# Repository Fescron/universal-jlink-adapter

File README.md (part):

# Universal J-Link Adapter

<br/>

<br/>

| Quick access links                                                                                                                                                                        |
| ----------------------------------------------------------------------------------------------------------------------------------------------------------------------------------------- |
| [Adapter v4.0 **schematic** (PDF)](hardware/jlink-tagConnect-adapter-v4/jlink-tagConnect-adapter-v4.pdf) // [Adapter v4.0 **gerber-files**](hardware/jlink-tagConnect-adapter-v4/Gerber/) |
| [Basic **J-Link Commander** usage and using **Segger Real-Time Transfer (RTT)** (instead of UART) for real-time debugging](JLinkExe-SeggerRTT-debugging-TipsTricks.md)                    |

<br/>

This multifunctional adapter board, primarily designed for use with a [J-Link debugger](https://www.segger.com/products/debug-probes/j-link/) (but others which follow the standard 20-pin JTAG/SWD pinout also work), allows the user to have the standard [9 pin Cortex-M SWD/JTAG pinout](https://www.segger.com/products/debug-probes/j-link/accessories/adapters/9-pin-cortex-m-adapter/) on both a 0.1" (2.54mm) and 0.05" (1.27mm) male pinheader. With additional jumpers it is possible to have **extra functionality** like **UART debugging though the J-Link's VCOM** on pins which normally aren't used in some modes, if the probe's hardware supports this. Good **labeling of all pin numbers and their corresponding functionality** also help to speed-up the embedded-development process. Additional information regarding the pinout of *default* SWD-headers as well as the voltage output of the J-Link debugger are also printed on the board, along with the pin-numbers of the [10 pin Tag-Connect header](http://www.tag-connect.com/TC2050-IDC).

Furthermore, the adapter PCB can **power the target board** through the `VTREF` connection. For this to work a **DC-DC converter or LDO regulator** can be plugged into the female 3-pin socket on the adapter board to allow the J-Link's 5V-Supply to be converted to, for example 3.3V. Various 3-pin voltage conversion boards are supported due to solder-jumpers available on the back of the adapter, allowing for the `VOUT`and `GND`pins to be swapped around. The 5V voltage can also be supplied *as-is* on a header pin by changing a jumper position.

Finally a physical reset button (with optional 100 Ω series-resistor and 100 nF filter capacitor) can be used to manually pull the reset line low, even if no debugger is connected. This eliminates the need to add a reset button to the target board and thus saves valuable board space.

The **0.05" (1.27mm) header** is recommended for when the target board is mostly connected to the debugger and the board in question also has a header of this size. The **0.1" (2.54mm) IDC header** is recommended for use with either regular jumper-wires or a [10 pin Tag-Connect adapter cable](http://www.tag-connect.com/TC2050-IDC). The latter allows target boards to be programmed without having to need a dedicated programming connector mounted, and thus saves on cost.

The figure on the left depicts the `TagConnect 2050` (*no-legs*) cable on the top-right, next to its corresponding footprint. Below this is a 0.05" header with its corresponding cable.

<br/>
<br/>

## 0 - Table of Contents

- [Universal J-Link Adapter](#universal-j-link-adapter)
  - [0 - Table of Contents](#0---table-of-contents)
  - [1 - Adapter functionality](#1---adapter-functionality)
    - [1.1 - Supply power to the target board (5V and/or other voltages)](#11---supply-power-to-the-target-board-5v-andor-other-voltages)
    - [1.2 - Additional functionality on "unused" pins using jumpers (and corresponding tips and tricks)](#12---additional-functionality-on-unused-pins-using-jumpers-and-corresponding-tips-and-tricks)
  - [2 - Serial flashing](#2---serial-flashing)
  - [3 - Layout guidelines for target boards](#3---layout-guidelines-for-target-boards)
  - [4 - BOM](#4---bom)
  - [5 - KiCad debug header symbols](#5---kicad-debug-header-symbols)

<br/>

## 1 - Adapter functionality

Aside from the ability to easily make connections to target boards using the well-labeled pinout and corresponding functionality of both output-headers, the following paragraphs give more information regarding additional features this adapter can provide.

<br/>

:pencil: **Note:** The pinout silkscreen has the following syntax:

- `... | ...`: The same (J-Link debugger) pin has different SWD or JTAG functionality
- `... / ...`: A jumper can be used to route one or the other signal to this pin
- `(...)`: This pin-signal deviates from the default SWD or JTAG pinout

<br/>

### 1.1 - Supply power to the target board (5V and/or other voltages)

As previously stated, a **DC-DC converter or LDO regulator** can be plugged into the 3-pin female header on this adapter with the labels `JP1 JP2 5V`. This would allow the adapter board to supply power through the `VTREF`-line (`PIN 1`) to the target board with the correct voltage, derived from the **5V supply of the J-Link debugger**. The 5V voltage can **also be made available *as-is* on** `PIN 5` of the output headers, by placing a jumper in the correct position of the header labeled `GND 5 5V`. With the same jumper `GND` can also be made available on `PIN 5`. Both the voltage-converter socket and `PIN 5`-jumper are depicted on the figure on the left.

If the user wishes to **not power the target board using** `VTREF`, for example in case of it already receiving power from a battery or external supply, the **voltage converter should simply not be plugged in**. The J-Link debugger will still receive the correct I/O voltage as a logic-level reference if the MCU's supply voltage is present on `VTREF` (`PIN 1`).

If the **pinout of the 3-pin voltage converter doesn't match** `VIN - VOUT - GND`, the last two pins can be changed around by swapping the solder joints on `JP1` and `JP2` on the bottom of the PCB. This is also also depicted on the figure on the left. If the present copper traces are cut on both jumpers and new solder connections are made on the opposite side, the pinout `VIN - GND - VOUT` will be selected.

<br/>

The **5V output needs to be enabled on the J-Link** using the [J-Link Commander](https://kb.segger.com/J-Link_Commander) software (`JLink.exe/JLinkExe`). The following command needs to be executed for the 5V supply to be always enabled:

```shell
Power On perm
```

<br/>

If the target board is powered via a voltage-converter on the adapter PCB, a jumper labeled `VTREF 1` below the 0.1" header allows for a **current meter** to be inserted between the converter and target board. This way its power usage can be monitored, for example in case the J-Link probe doesn't have this functionality build-in. If 5V is supplied to the target board through `PIN 5`, a jumper in this location can also be substituted for a current meter. Both headers are depicted on the figure on the right.

<br/>

### 1.2 - Additional functionality on "unused" pins using jumpers (and corresponding tips and tricks)

In addition to the *default* SWD or JTAG pinouts it is also possible to add extra functionality to normally *unused* pins of the 02x05 headers:

- :pushpin: **PIN 5** is normally connected to `GND`.
  - On the [Segger 10 pin Needle Adapter](https://www.segger.com/products/debug-probes/j-link/accessories/adapters/10-pin-needle-adapter/) this pin outputs the J-Link's `5V-Supply`. A jumper on the adapter board can be used to select this, which was already mentioned in the previous section.
  - :bulb: **TIP:** See the [following section](#2---serial-flashing) to use this pin for **serial programming**.
- :pushpin: **PIN 6** is normally used for the `SWO` or `TDO` connection. A jumper labeled `SWO TDO 6`, which can be seen on the figure on the right, can however be used to disconnect the debugger from the target board.
  - :bulb: **TIP:** Disconnecting the pin from the debugger can enable the MCU's output pin to be used as a GPIO debug signal. It can for example be set high if some code is running, and low when this is not the case. Simply remove the jumper and add a jumper-wire on the pin labeled `6`.
- :pushpin: **PIN 7** is on the [standard 9-pin Cortex-M SWD/JTAG pinout](https://www.segger.com/products/debug-probes/j-link/accessories/adapters/9-pin-cortex-m-adapter/) *not populated* since this is the **key**.
  - **SWD mode:** A jumper labeled `RTCK 7 JL.RX` can be used to connect this pin to the J-Link's **VCOM** `RX` pin. This way UART debugging can be used in conjunction with SWD.
    - :bulb: **TIP:** The jumper can also be removed, and a separate UART `TXD` signal from a target board can be connected to the J-Link's `RX` input by connecting a jumper-wire to the `JL.RX` pin.
    - :pencil: **NOTE:** It is possible VCOM needs to be enabled on the probe. This can be done using [J-Link Commander](https://kb.segger.com/J-Link_Commander) (`JLinkExe/JLink.exe`) by executing the following command (VCOM will start working after the next power-cycle):
      ```shell
      VCOM enable
      ```
  - **JTAG mode:** The same jumper can also be used to connect this pin to `RTCK` if necessary.
- :pushpin: **PIN 8**
  - **SWD mode:** Normally this pin is *not connected*, but a jumper labeled `JL.TX TDI 8` allows it to be connected to the J-Link's **VCOM** `TX` pin.
    - :bulb: **TIP:** The jumper can also be removed, and a separate UART `RXD` signal from a target board can be connected to the J-Link's `TX` output by connecting a jumper-wire to the `JL.TX` pin.
  - **JTAG mode:** On Segger's [9 pin](https://www.segger.com/products/debug-probes/j-link/accessories/adapters/9-pin-cortex-m-adapter/) and [19 pin](https://www.segger.com/products/debug-probes/j-link/accessories/adapters/19-pin-cortex-m-adapter/) Cortex-M adapters `PIN 9` is connected to `TDI`.
    - :bulb: **TIP:** The `TDI` signal of a J-Link debugger can be set *low* or *high* using **J-Link Commander** by executing `TDI0` and `TDI1` respectively, even if there is no target connection active. This signal can thus be used as a GP(I)O line to, for example, an MCU input pin.
  - :pencil: **NOTE:** `JL.TX` and `TDI` are for both modes located on the same physical J-Link pin. This means the jumper should normally not need to be disconnected when using the adapter in one or the other mode.
- :pushpin: **PIN 9**
  - **SWD mode:** Normally this pin is *not connected*. Sometimes a target board however uses this pin as `GNDdetect`, so it can (as the name implies) detect the presence of a debugger. With a jumper labeled `nTRST 9 GND` this pin can be connected to `GND` to enable this functionality.
    - :bulb: **TIP:** When `PIN 9` is connected to a microcontroller pin which can act as an output, the adapter can be used to *break-out* this pin to another instrument for, for example, code-timing analysis. Simply remove the jumper and add a jumper-wire on the pin labeled `9`.
  - **JTAG mode:** On Segger's [9 pin](https://www.segger.com/products/debug-probes/j-link/accessories/adapters/9-pin-cortex-m-adapter/) and [19 pin](https://www.segger.com/products/debug-probes/j-link/accessories/adapters/19-pin-cortex-m-adapter/) Cortex-M adapters this pin can be connected to `nTRST` using a solder jumper. On this adapter board this can be done using a regular jumper.
    - :bulb: **TIP:** The `nTRST` signal of a J-Link debugger can be set *low* or *high* using **J-Link Commander** by executing `TRST0` and `TRST1` respectively, even if there is no target connection active. This signal can thus be used as a GP(I)O line to, for example, an MCU input pin.
- :pushpin: **PIN 10** is used to reset the target board. A jumper is present to disconnect this line if necessary.
  - :bulb: **TIP:** The `nRESET` signal of a J-Link debugger can be set *low* or *high* using **J-Link Commander** by executing `R0` and `R1` respectively, even if there is no target connection active.<br/>
  - An `nRESET` button is also present on the adapter board to manually pull the reset line low. An optional (100 Ω) series-resistor `R1` and (100 nF) filter capacitor C1 can be mounted on the bottom of the board, both in the 0603 package. They are depicted on the figure on the right. To *activate* the functionality of `R1` jumper `JP10` has to be cut.

<br/>

:bulb: **TIP:** `ShowHWStatus` or `ST` can be executed in **J-Link Commander** to show the current `VTREF` voltage as well as the signal-level of the `SWCLK|TCK`, `TDI`, `SWO|TDO`, `SWDIO|TMS`, `nRESET` (`TRES`) and `nTRST` pins, even if there is no target connection active.

Additionally a two-pin `GND` header, next to the `JL.TX TDI 8` jumper, also facilitates some additional ground-wire connections for general debug connections.

<br/>

<br/>

## 2 - Serial flashing

Due to the availability of the jumpers on the adapter PCB certain pins can also be used to detect if a target board is plugged in. A board such as the [Macropedal](https://github.com/Fescron/macropedal) can for example be used to check if `pin 5` is, via a target board, connected to ground. If this is the case, the *Macropedal* can enter a command in a terminal to flash firmware to a board. This way one after the other board can be programmed in a **series production** scenario. The target board can even be powered by the adapter itself for a complete *stand-alone* setup. The figure on the right depicts such an arrangement. Refer to [Segger J-Link debugging tips & tricks - 2 - Scripting](JLinkExe-SeggerRTT-debugging-TipsTricks.md#2---scripting) for more information.

<br/>

## 3 - Layout guidelines for target boards

It is advised to add the following passives to the *target board* for protection and stability. This is also mentioned on the [adapter schematic](hardware/jlink-tagConnect-adapter-v4/jlink-tagConnect-adapter-v4.pdf).

- 10 kΩ pullup on `SWDIO|TMS`, `TDO` and `TDI` (and the target board's `RXD` line)
- 10 kΩ pulldown on `SWCLK|TCK`
- 33 to 100 Ω in-line current-limiting resistors on `TXD` and `RXD` lines
  - This can be important for when UART is available on a (0.1") external header, and is less important if this is made available on the SWD-header. 100 pF capacitors (*after* the series resistors) can also help with some filtering and ESD mitigation.

<br/>

## 4 - BOM

| Component              | Footprint                                                | Manufacturer `Partnumber`      | Ordering                                                                                                                 |
| ---------------------- | -------------------------------------------------------- | ------------------------------ | ------------------------------------------------------------------------------------------------------------------------ |
| J1                     | 02x10 0.1" (2.54mm) Right Angle Keyed Female IDC Socket  | Sullins `SFH11-PBPC-D10-RA-BK` | [digikey.be](https://www.digikey.be/product-detail/en/sullins-connector-solutions/SFH11-PBPC-D10-RA-BK/S9205-ND/1990098) |
| J2                     | 02x05 0.1" Male Key-Shrouded IDC Header                  | Samtec `TST-105-01-L-D`        | [digikey.be](https://www.digikey.be/en/products/detail/samtec-inc/TST-105-01-L-D/2685818)                                |
| J3                     | 02x05 0.05" (1.27mm) Male Key-Shrouded Header            | Samtec `FTSH-105-01-L-D-K`     | [digikey.be](https://www.digikey.be/en/products/detail/samtec-inc/FTSH-105-01-L-D-K/2649979)                             |
| J4                     | 01x03 0.1" Female IDC Socket                             | Samtec `SSW-103-01-G-S`        | [digikey.be](https://www.digikey.be/en/products/detail/samtec-inc/SSW-103-01-G-S/1112104)                                |
| J5, JP4, JP5, JP8, JP9 | 01x02 0.1" Male IDC Header                               | Samtec `TSW-102-07-L-S`        | [digikey.be](https://www.digikey.be/en/products/detail/samtec-inc/TSW-102-07-L-S/1101425)                                |
| JP3, JP6, JP7          | 01x03 0.1" Male IDC Header                               | Samtec `TSW-103-07-L-S`        | [digikey.be](https://www.digikey.be/en/products/detail/samtec-inc/TSW-103-07-L-S/1101424)                                |
| SW1                    | 6.5mm Pitch Through-hole Switch                          | C&K `PTS636SL43 LFS`           | [digikey.be](https://www.digikey.be/en/products/detail/c-k/PTS636SL43-LFS/10071714)                                      |
| R1                     | 100 Ω 0603 1% (1 kΩ should also work)                    | Yageo `RC0603FR-07100RL`       | [digikey.be](https://www.digikey.be/en/products/detail/yageo/RC0603FR-07100RL/726888)                                    |
| C1                     | 100 nF 0603 10% 50V X7R                                  | Yageo `CC0603KRX7R9BB104`      | [digikey.be](https://www.digikey.be/en/products/detail/yageo/CC0603KRX7R9BB104/2103082)                                  |
|                        | 2.54mm Pitch Jumpers                                     | Samtec `SNT-100-BK-G`          | [digikey.be](https://www.digikey.be/en/products/detail/samtec-inc/SNT-100-BK-G/1756763)                                  |
|                        | 02x05 0.05" IDC Cable, 6 inch (15 cm) Long               | Samtec `FFSD-05-D-06.00-01-N`  | [digikey.be](https://www.digikey.be/en/products/detail/samtec-inc/FFSD-05-D-06-00-01-N/1106577)                          |
|                        | TagConnect 10 pin IDC to Needles Without Legs (`...-NL`) | TagConnect `TC-2050-IDC-NL`    | [digikey.be](https://www.digikey.be/product-detail/nl/tag-connect-llc/TC2050-IDC-NL/TC2050-IDC-NL-ND/2605367)            |
|                        | TagConnect 10 pin IDC to Needles                         | TagConnect `TC-2050-IDC`       | [digikey.be](https://www.digikey.be/en/products/detail/tag-connect-llc/TC2050-IDC/2605366)                               |

<br/>

## 5 - KiCad debug header symbols

On the repository [brechtve-kicad-things](https://github.com/Fescron/brechtve-kicad-things) symbols are available where the additional functionality, selectable using the jumpers, is depicted for both SWD and JTAG modes. The *regular* pinouts are put into brackets. The symbols can be found in the library [`BrechtVE_DebugHeader.lib`](https://github.com/Fescron/brechtve-kicad-things/blob/master/Libraries/BrechtVE_DebugHeader.lib).

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
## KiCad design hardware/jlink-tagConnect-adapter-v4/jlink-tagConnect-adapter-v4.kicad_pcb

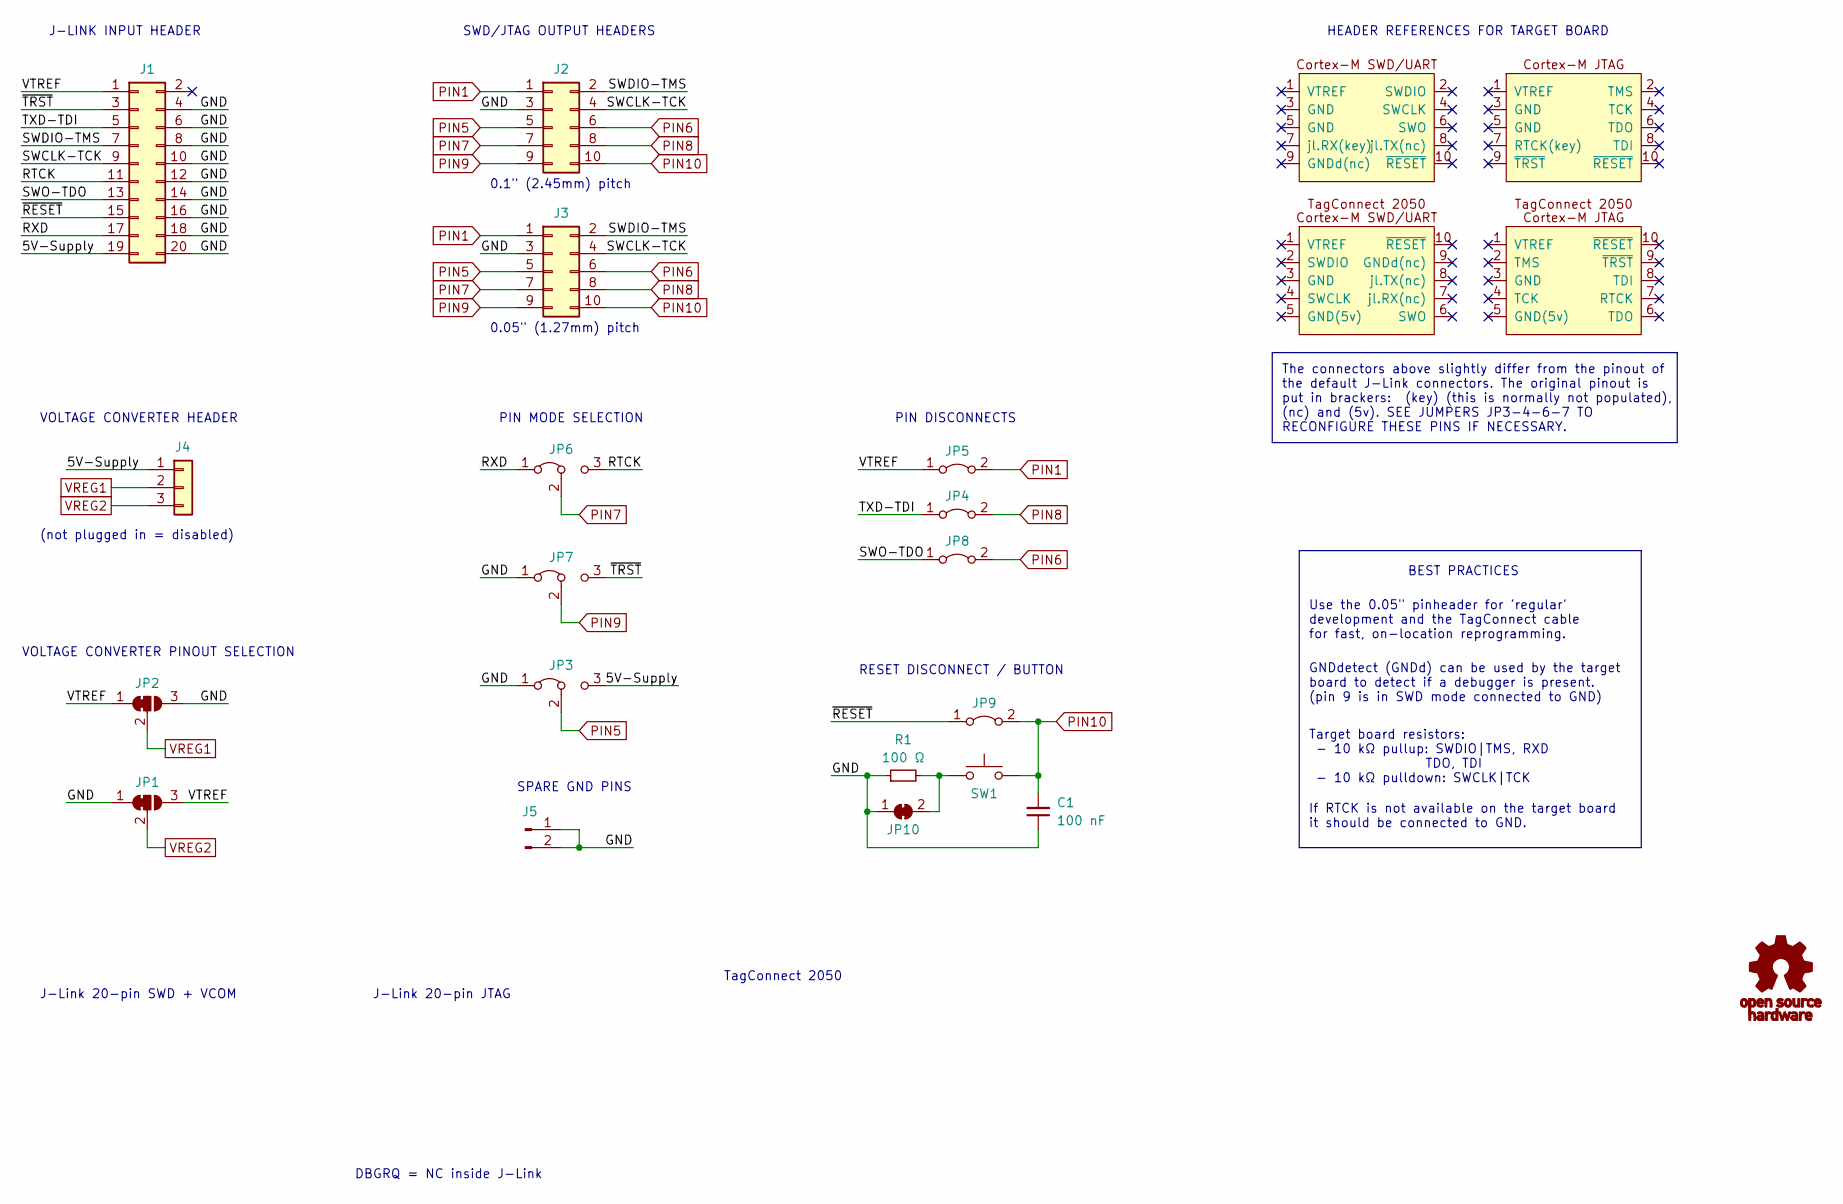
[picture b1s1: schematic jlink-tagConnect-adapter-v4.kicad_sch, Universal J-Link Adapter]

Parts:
C1: 100 nF; C_0603_1608Metric_Pad1.08x0.95mm_HandSolder
G1: Symbol_OSHW-Logo_11.4x12mm; OSHW-Logo_5.7x6mm_SolderMask
J1: Conn_02x10_Odd_Even; PinSocket_2x10_P2.54mm_Horizontal
J2: Conn_02x05_Odd_Even; IDC-Header_2x05_P2.54mm_Vertical
J3: Conn_02x05_Odd_Even; PinHeader_2x05_P1.27mm_Vertical
J4: Conn_01x03; PinSocket_1x03_P2.54mm_Vertical
J5: Conn_01x02_Pin; PinHeader_1x02_P2.54mm_Vertical
JP1, JP2: SolderJumper_3_Bridged12; SolderJumper-3_P1.3mm_Bridged12_Pad1.0x1.5mm_NumberLabels
JP3, JP6, JP7: Jumper_3_Bridged12; PinHeader_1x03_P2.54mm_Vertical
JP4, JP5, JP8, JP9: Jumper_2_Bridged; PinHeader_1x02_P2.54mm_Vertical
JP10: SolderJumper_2_Bridged; SolderJumper-2_P1.3mm_Bridged_Pad1.0x1.5mm
R1: 100 Ω; R_0603_1608Metric_Pad0.98x0.95mm_HandSolder
SW1: SW_Push; SW_PUSH_1P1T_6x3.5mm_H4.3_APEM_MJTP1243

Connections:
/5V-Supply: J1.19, J4.1, JP3.3 (B)
/GND: C1.1, J1.4, J1.6, J1.8, J1.10, J1.12, J1.14, J1.16, J1.18, J1.20, J2.3, J3.3, J5.1, J5.2, JP1.1 (A), JP2.3 (B), JP3.1 (A), JP7.1 (A), JP10.1 (A), R1.1
/RTCK: J1.11, JP6.3 (B)
/RXD: J1.17, JP6.1 (A)
/SWCLK-TCK: J1.9, J2.4, J3.4
/SWDIO-TMS: J1.7, J2.2, J3.2
/SWO-TDO: J1.13, JP8.1 (A)
/TXD-TDI: J1.5, JP4.1 (A)
/VTREF: J1.1, JP1.3 (B), JP2.1 (A), JP5.1 (A)
/~RESET: J1.15, JP9.1 (A)
/~TRST: J1.3, JP7.3 (B)
unnamed: JP10.2 (B), R1.2, SW1.1
PIN1: J2.1, J3.1, JP5.2 (B)
PIN5: J2.5, J3.5, JP3.2 (C)
PIN6: J2.6, J3.6, JP8.2 (B)
PIN7: J2.7, J3.7, JP6.2 (C)
PIN8: J2.8, J3.8, JP4.2 (B)
PIN9: J2.9, J3.9, JP7.2 (C)
PIN10: C1.2, J2.10, J3.10, JP9.2 (B), SW1.2
VREG1: J4.2, JP2.2 (C)
VREG2: J4.3, JP1.2 (C)

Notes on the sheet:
(not plugged in = disabled)
VOLTAGE CONVERTER PINOUT SELECTION
TagConnect 2050
GNDdetect (GNDd) can be used by the target board to detect if a debugger is present. (pin 9 is in SWD mode connected to GND)
0.1" (2.45mm) pitch
PIN DISCONNECTS
0.05" (1.27mm) pitch
SPARE GND PINS
BEST PRACTICES
RESET DISCONNECT / BUTTON
PIN MODE SELECTION
DBGRQ = NC inside J-Link
The connectors above slightly differ from the pinout of the default J-Link connectors. The original pinout is put in brackers: (key) (this is normally not populated), (nc) and (5v). SEE JUMPERS JP3-4-6-7 TO RECONFIGURE THESE PINS IF NECESSARY.
SWD/JTAG OUTPUT HEADERS
J-Link 20-pin JTAG
J-LINK INPUT HEADER
HEADER REFERENCES FOR TARGET BOARD
VOLTAGE CONVERTER HEADER
If RTCK is not available on the target board it should be connected to GND.
Use the 0.05" pinheader for 'regular' development and the TagConnect cable for fast, on-location reprogramming.
J-Link 20-pin SWD + VCOM
Target board resistors: - 10 kΩ pullup: SWDIO|TMS, RXD TDO, TDI - 10 kΩ pulldown: SWCLK|TCK

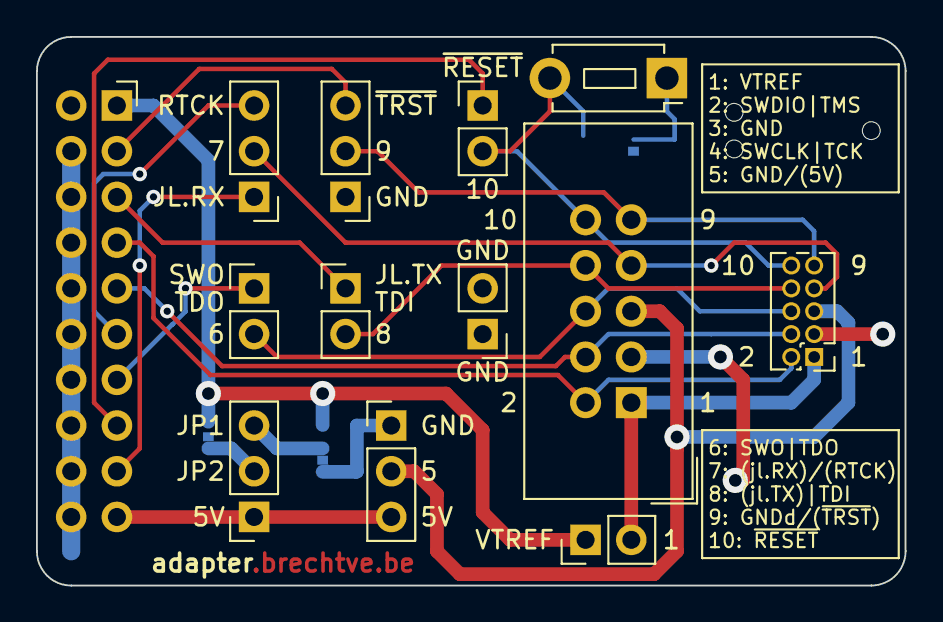
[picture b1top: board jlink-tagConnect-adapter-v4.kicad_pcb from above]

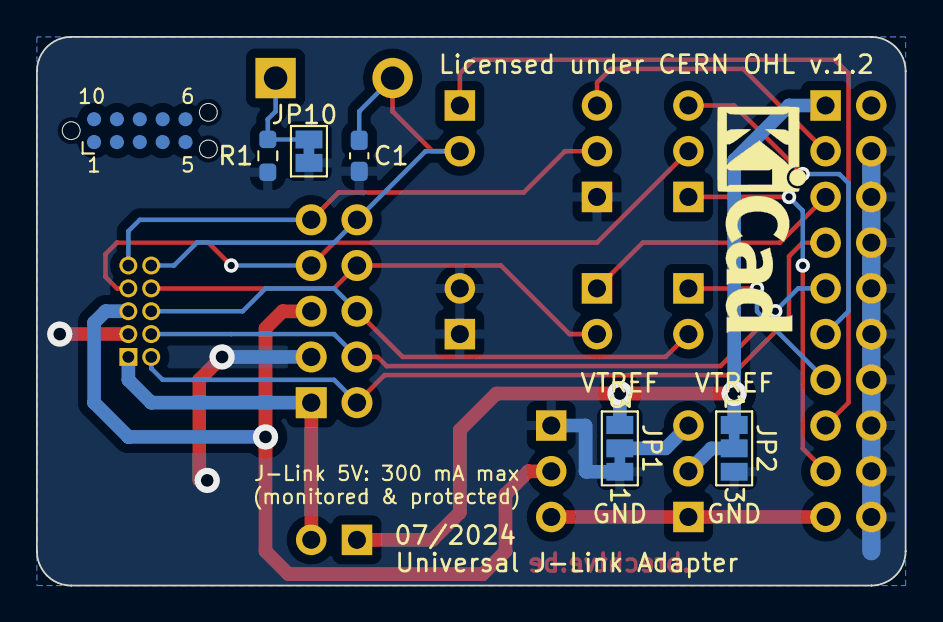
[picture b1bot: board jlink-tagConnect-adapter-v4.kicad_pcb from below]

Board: 2 copper layers, 48.3 x 30.5 mm, 19 parts (6 on the bottom side), 21 nets.

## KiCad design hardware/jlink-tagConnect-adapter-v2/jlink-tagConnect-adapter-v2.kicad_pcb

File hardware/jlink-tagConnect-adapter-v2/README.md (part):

# Universal J-Link Adapter

<br/>

<br/>

- [Quick link to the schematic](hardware/jlink-tagConnect-adapter-v2/jlink-tagConnect-adapter-v2.pdf)

<br/>

This multifunctional adapter board, primarily designed for use with a [J-Link debugger](https://www.segger.com/products/debug-probes/j-link/models/j-link-base/) (or others which follow its standard 20-pin JTAG/SWD pinout), allows the user to have the standard [9 pin Cortex-M SWD/JTAG pinout](https://www.segger.com/products/debug-probes/j-link/accessories/adapters/9-pin-cortex-m-adapter/) on both a 0.1" (2.54mm) and 0.05" (1.27mm) header. With additional jumpers, it's possible to have **extra options (for example UART debugging though the J-Link's VCOM) on pins that normally aren't used in some modes**. The adapter can also **power the target board** through `VTREF`. A DC-DC converter can be plugged in on the adapter to allow the J-Link's `5V-Supply` to be converted to, for example 3.3V.

The **0.05" header** is recommended for development when the target board is mostly connected to the debugger. The **0.1" IDC header** is recommended for use with a [10 pin Tag-Connect adapter cable](http://www.tag-connect.com/TC2050-IDC), so target boards can quickly be reprogrammed *on-location*.

On the picture next to this text on top you can see this TagConnect 2050 cable next to its corresponding PCB footprint. Below you can see the 0.05" header with its corresponding cable.

<br/>

A lot of useful information is also printed on the *silkscreen* of the PCB. Noteworthy is the **pinout numbering** of the 0.1" and 0.05" headers (wich are connected to SWD/JTAG pins) and also the numbering of the 10-pin Tag-Connect header on the front. The **functions for every pin** are also printed on the back of the PCB.

<br/>

## 1 - Functions

### 1.1 - Supply power to a target board

A **DC-DC converter** can be plugged in on the header with the labels `5V JP6 JP7` to supply the target board with the correct voltage, derived from the 5V supply of the J-Link programmer. If the pinout of the converter doesn't match `VIN - VOUT - GND`, the last two pins can be changed around by swapping the solder joints on `JP6` and `JP7` on the bottom of the PCB. Then the pinout `VIN - GND - VOUT` will be selected.

This 5V output needs to be enabled on the J-Link using the `J-Link Commander` (`JLinkExe`) software. The following command needs to be called for the 5V supply to be always enabled:

```shell
power on perm
```

If the user wishes to **not power the target board using `VTREF`** (for example in the case that the target board is already getting its own power from a battery), the **DC-DC converter should simply not be plugged in**.

<br/>

**PIN 1** (`VTREF`) normally supplies the J-Link adapter with a voltage to allow it to generate the correct logic levels. With this adapter board the target board can be powered through `VTREF` using the previously mentioned DC-DC converter. A jumper is supplied below the 0.1" header to allow a **current meter** to be plugged in-line between the DC-DC converter and the target board so the power usage can be monitored.

<br/>

### 1.2 - Additional functionality on unused pins using jumpers

- **PIN 5** is normally connected to GND.
  - On the [J-Link 10 pin Needle Adapter](https://www.segger.com/products/debug-probes/j-link/accessories/adapters/10-pin-needle-adapter/) this pin outputs the J-Link's `5V-Supply`. A jumper can be used to select this.
- **PIN 7** is on the [standard 9-pin Cortex-M SWD/JTAG pinout](https://www.segger.com/products/debug-probes/j-link/accessories/adapters/9-pin-cortex-m-adapter/) *not populated* since this is the **key**.
  - **SWD mode:** A jumper can be used to connect this pin to the J-Link's VCOM `RX` pin, so UART debugging functionality can be used in conjunction with SWD.
  - **JTAG mode:** The same jumper can also be used to connect this pin to `RTCK` if necessary.
- **PIN 8**
  - **SWD mode:** Normally this pin is *not connected*, but a jumper allows it to be connected to the J-Link's VCOM `TX` pin.
  - **JTAG mode:** On J-Link's [9 pin](https://www.segger.com/products/debug-probes/j-link/accessories/adapters/9-pin-cortex-m-adapter/) and [19 pin](https://www.segger.com/products/debug-probes/j-link/accessories/adapters/19-pin-cortex-m-adapter/) Cortex-M adapters this pin is connected to `TDI`.
  - *NOTE:* `TX` and `TDI` are in both modes on the same pin. This means that normally this pin shouldn't be disconnected but a jumper allows this just in case.
- **PIN 9**
  - **SWD mode:** Normally this pin is *not connected*, but sometimes a target board uses this pin as `GNDdetect` so it can detect the presence of a debugger. With a jumper this pin can be connected to GND to enable this functionality.
  - **JTAG mode:** On J-Link's [9 pin](https://www.segger.com/products/debug-probes/j-link/accessories/adapters/9-pin-cortex-m-adapter/) and [19 pin](https://www.segger.com/products/debug-probes/j-link/accessories/adapters/19-pin-cortex-m-adapter/) Cortex-M adapters this pin can be connected to `nTRST` using a solder jumper. On this adapter board this can be done using a regular jumper.

<br/>

## 2 - KiCad debug header symbols

On the repository [brechtve-kicad-things](https://github.com/Fescron/brechtve-kicad-things) (kicad.brechtve.be) you can find some symbols (and a lot of additional information regarding KiCad) where these additional functions, selectable using the jumpers, are depicted for both SWD and JTAG modes. They can be found in the library `BrechtVE_DebugHeader.lib`. The symbols can be linked to a 0.05" header on the target board and are:

<br/>
<br/>

Symbols are also supplied that can be linked to a TagConnect 2050 footprint. The pin numbers and corresponding functions are mostly the same as the previously mentioned SWD/JTAG connectors, but the direction in wich the pins are layed out on the PCB are different. This is reflected in other symbols:

<br/>
<br/>

For reference, these symbols (and additional information regarding for example jumpers and layout guidelines) can be found on the [adapter schematic](hardware/jlink-tagConnect-adapter-v2/jlink-tagConnect-adapter-v2.pdf).

<br/>

## 3 - Layout guidelines for target board

It's advised to add the following passives on the *target board* for protection and stability:
- 100 kΩ pullup on `SWDIO`.
- 10 kΩ pullup on `RXD`.
- 100 Ω inline current limiting resistors on `TXD` and`RXD` lines (mostly used for additional external headers)

<br/>

## 4 - BOM

- 0.1" = 2.54mm
- 0.05" = 1.27mm

| Component     | Footprint                                                | Type                             | Ordering                                                                                                                                                 |
| ------------- | -------------------------------------------------------- | -------------------------------- | -------------------------------------------------------------------------------------------------------------------------------------------------------- |
| J1            | 02x10 0.1" Right Angle Female IDC socket                 | Sullins `SFH11-PBPC-D10-RA-BK`   | [digiKey.be](https://www.digikey.be/product-detail/en/sullins-connector-solutions/SFH11-PBPC-D10-RA-BK/S9205-ND/1990098)                                 |
|               | 02x10 0.1" Right Angle Female socket                     | Samtec `SSW-110-02-L-D-RA`       | [mouser.be](https://www.mouser.be/ProductDetail/Samtec/SSW-110-02-L-D-RA?qs=sGAEpiMZZMvffgRu4KC1RxM6nKwEP14AKIDk%2F38Cqz31wxmPLBdGrA%3D%3D)              |
| J2            | 02x05 0.1" Male IDC header                               | Samtec `TST-105-01-L-D`          | [mouser.be](https://www.mouser.be/ProductDetail/Samtec/TST-105-01-L-D?qs=sGAEpiMZZMvlX3nhDDO4AI%252BRmCAOnNK%252B8W%2Fig2WTmT0%3D)                       |
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
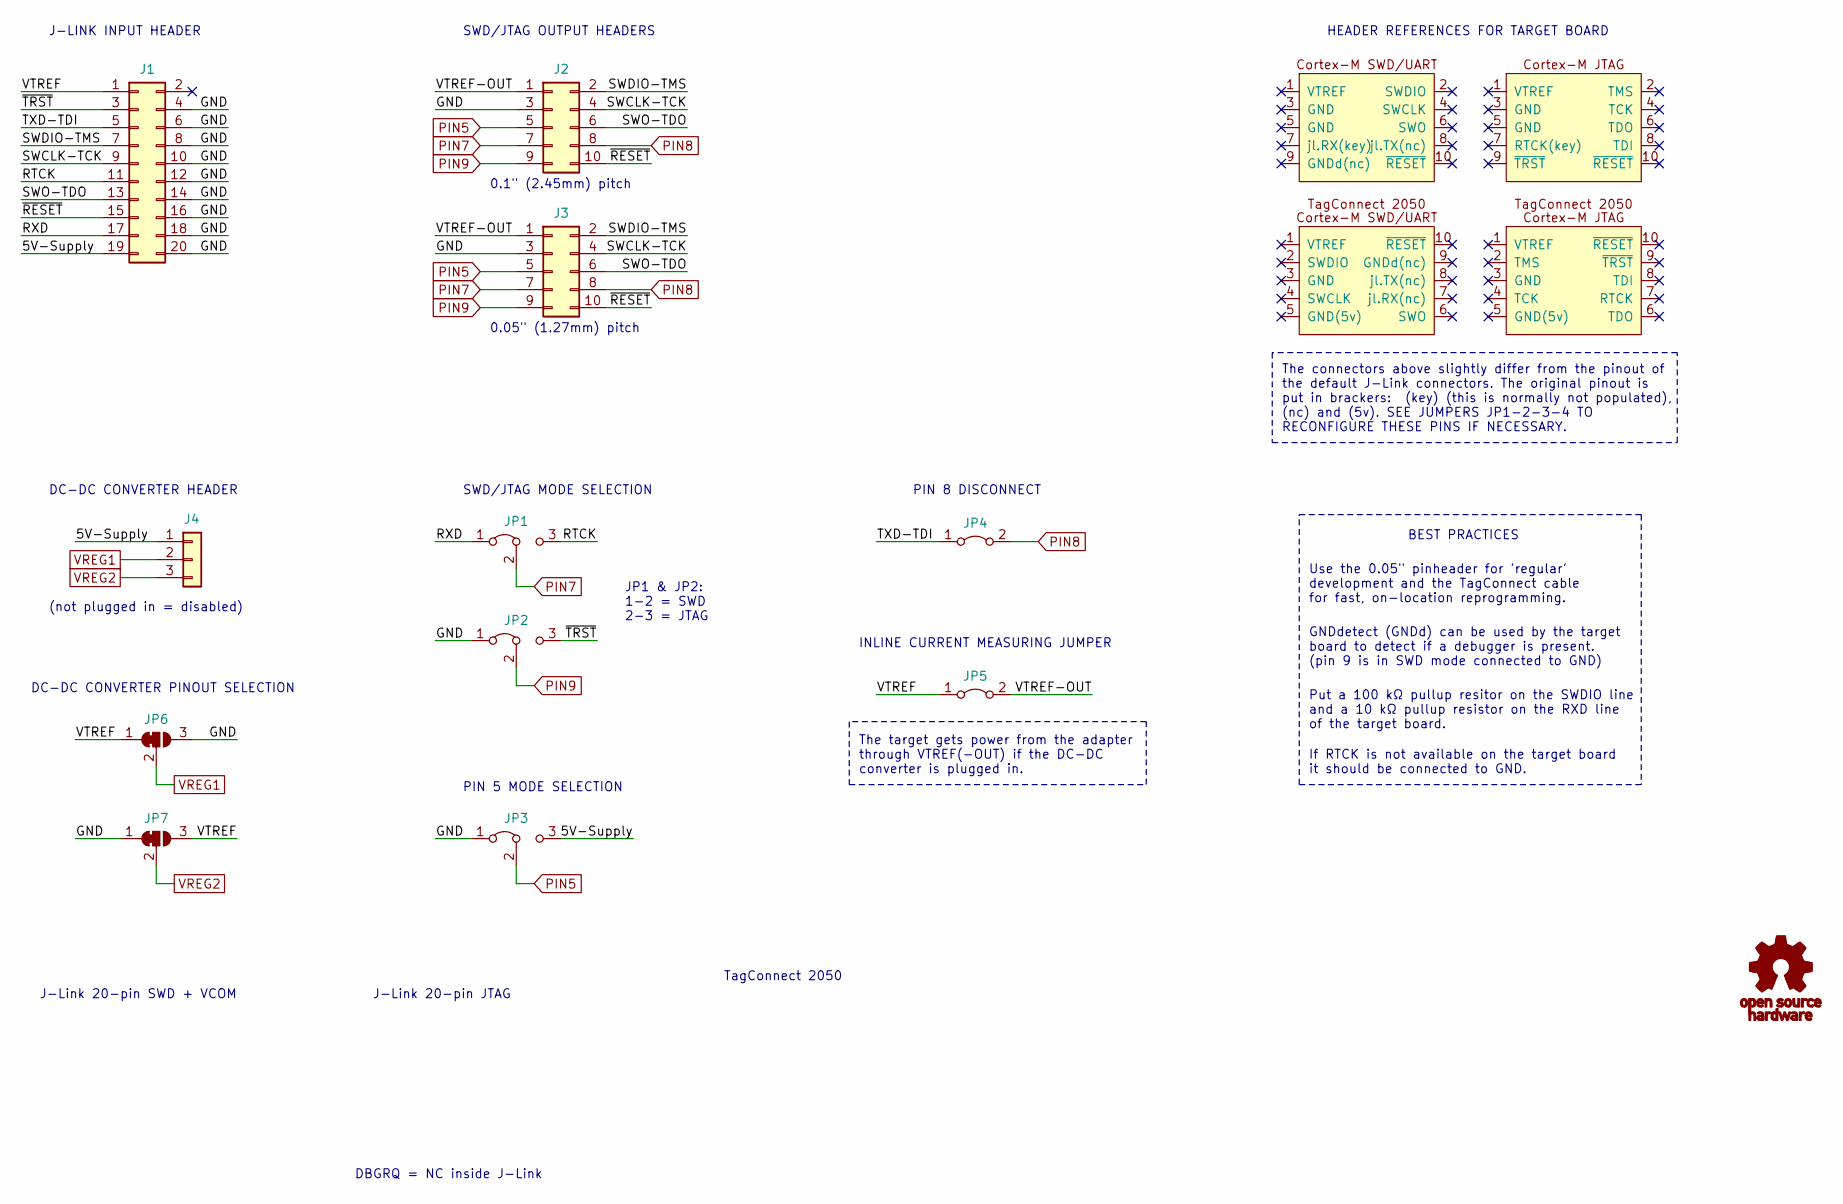
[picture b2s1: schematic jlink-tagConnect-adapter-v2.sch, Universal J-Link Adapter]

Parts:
G1: Symbol_OSHW-Logo_11.4x12mm; OSHW-Logo_5.7x6mm_SolderMask
J1: Conn_02x10_Odd_Even; PinSocket_2x10_P2.54mm_Horizontal
J2: Conn_02x05_Odd_Even; IDC-Header_2x05_P2.54mm_Vertical
J3: Conn_02x05_Odd_Even; PinHeader_2x05_P1.27mm_Vertical_SMD
J4: Conn_01x03; PinSocket_1x03_P2.54mm_Vertical
JP1, JP2, JP3: Jumper_3_Bridged12; PinHeader_1x03_P2.54mm_Vertical
JP4, JP5: Jumper_2_Bridged; PinHeader_1x02_P2.54mm_Vertical
JP6, JP7: SolderJumper_3_Bridged12; SolderJumper-3_P1.3mm_Bridged12_Pad1.0x1.5mm_NumberLabels

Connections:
/5V-Supply: J1.19, J4.1, JP3.3 (B)
/GND: J1.4, J1.6, J1.8, J1.10, J1.12, J1.14, J1.16, J1.18, J1.20, J2.3, J3.3, JP2.1 (A), JP3.1 (A), JP6.3 (B), JP7.1 (A)
/RTCK: J1.11, JP1.3 (B)
/RXD: J1.17, JP1.1 (A)
/SWCLK-TCK: J1.9, J2.4, J3.4
/SWDIO-TMS: J1.7, J2.2, J3.2
/SWO-TDO: J1.13, J2.6, J3.6
/TXD-TDI: J1.5, JP4.1 (A)
/VTREF: J1.1, JP5.1 (A), JP6.1 (A), JP7.3 (B)
/VTREF-OUT: J2.1, J3.1, JP5.2 (B)
/~RESET: J1.15, J2.10, J3.10
/~TRST: J1.3, JP2.3 (B)
PIN5: J2.5, J3.5, JP3.2 (C)
PIN7: J2.7, J3.7, JP1.2 (C)
PIN8: J2.8, J3.8, JP4.2 (B)
PIN9: J2.9, J3.9, JP2.2 (C)
VREG1: J4.2, JP6.2 (C)
VREG2: J4.3, JP7.2 (C)

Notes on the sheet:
J-Link 20-pin JTAG
J-Link 20-pin SWD + VCOM
DBGRQ = NC inside J-Link
J-LINK INPUT HEADER
HEADER REFERENCES FOR TARGET BOARD
TagConnect 2050
0.1" (2.45mm) pitch
0.05" (1.27mm) pitch
SWD/JTAG OUTPUT HEADERS
SWD/JTAG MODE SELECTION
JP1 & JP2: 1-2 = SWD 2-3 = JTAG
INLINE CURRENT MEASURING JUMPER
DC-DC CONVERTER HEADER
(not plugged in = disabled)
Use the 0.05" pinheader for 'regular' development and the TagConnect cable for fast, on-location reprogramming.
BEST PRACTICES
Put a 100 kΩ pullup resitor on the SWDIO line and a 10 kΩ pullup resistor on the RXD line of the target board.
If RTCK is not available on the target board it should be connected to GND.
GNDdetect (GNDd) can be used by the target board to detect if a debugger is present. (pin 9 is in SWD mode connected to GND)
The connectors above slightly differ from the pinout of the default J-Link connectors. The original pinout is put in brackers: (key) (this is normally not populated), (nc) and (5v). SEE JUMPERS JP1-2-3-4 TO RECONFIGURE THESE PINS IF NECESSARY.
The target gets power from the adapter through VTREF(-OUT) if the DC-DC converter is plugged in.
PIN 5 MODE SELECTION
PIN 8 DISCONNECT
DC-DC CONVERTER PINOUT SELECTION

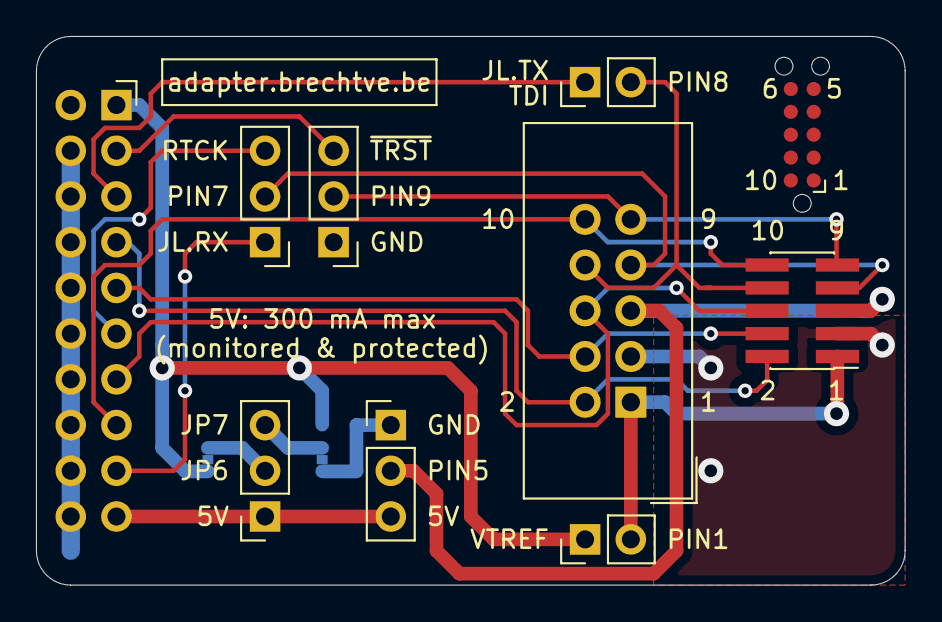
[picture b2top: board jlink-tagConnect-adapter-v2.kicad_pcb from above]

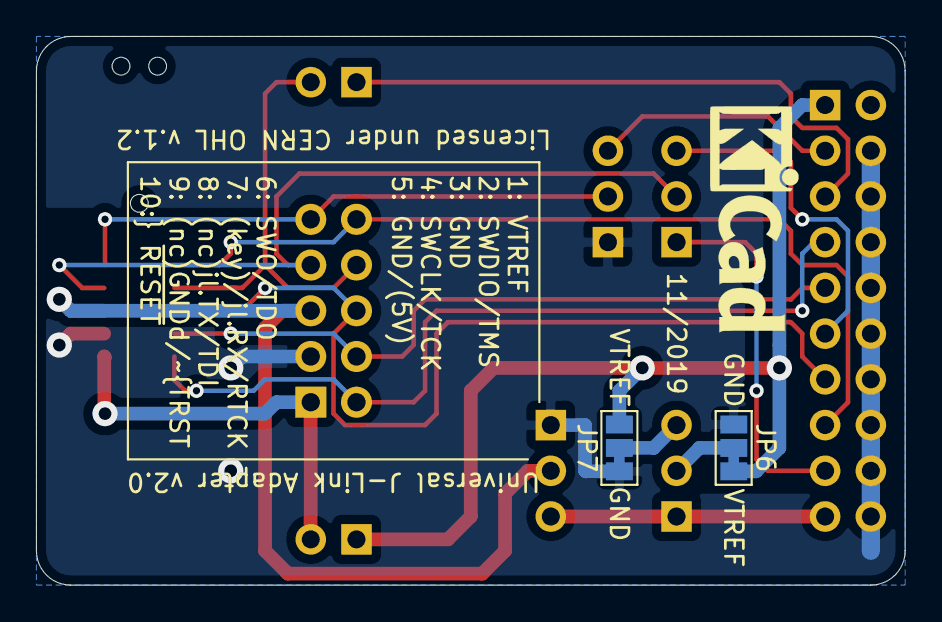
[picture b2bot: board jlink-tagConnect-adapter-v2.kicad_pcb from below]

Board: 2 copper layers, 48.3 x 30.5 mm, 12 parts (2 on the bottom side), 18 nets.

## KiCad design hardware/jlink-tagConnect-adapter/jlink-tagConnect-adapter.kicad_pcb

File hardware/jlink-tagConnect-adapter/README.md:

# jlink-tagConnect-adapter v1.0

<br/>

**This is an old version of the board and was never really used since it didn't follow the J-Link Needle adapter pinout. It's kept here for documentation purposes.**

- [Schematic](hardware/jlink-tagConnect-adapter/jlink-tagConnect-adapter.pdf)

<br/>

## 1 - Usage

One can plug this *4cm x 5cm* adapter board in a [J-Link debugger](https://www.segger.com/products/debug-probes/j-link/models/j-link-base/) along with a [10 pin Tag-Connect adapter cable](http://www.tag-connect.com/TC2050-IDC) on the IDC connector. The cable will then have the approximate pinout (`RXD` instead of pin 7 `NC`) of the [standard 9-pin Cortex-M SWD/JTAG pinout](https://www.segger.com/products/debug-probes/j-link/accessories/adapters/9-pin-cortex-m-adapter/) from J-Link. The pinout of the Tag-Connect cable can be seen on the picure below (and for reference also on the bottom of the adapter board, but its pins aren't connected).

- **Pinheaders** `J1` and `J2` can be used to break out the SWD/JTAG pins to a 2.54mm standard header.
- **Pushbutton** `SW1` can be used to mannually **reset** the target board.
- A **DC-DC converter** can be plugged in on header `J4` to supply the target board with the correct voltage using the 5V supply of the J-Link programmer.
  - If the pinout of the converter doesn't match `VIN - VOUT - GND`, the last two pins can be changed around by swapping the solder joints on `JP1` and `JP2` on the bottom of the adapter. Then the pinout `VIN - GND - VOUT` will be selected.
- **Jumpers** `J6` and `J7` can also be used to swap some pinouts around. `J6` connects `pin 4` on the Tag-Connect cable to `RXD` or *doesn't connect it*. `J7` connects `pin 5` on the Tag-Connect cable to *nothing* or to `nTRST` (JTAG).

<br/>

## 2 - BOM

| Component | Value                                                                                                                                                   |
| --------- | ------------------------------------------------------------------------------------------------------------------------------------------------------- |
| J1        | 01x07 Male pinheader                                                                                                                                    |
| J2        | 01x03 Male pinheader                                                                                                                                    |
| J3        | 02x10 Female IDC connector ([DigiKey link](https://www.digikey.be/product-detail/en/sullins-connector-solutions/SFH11-PBPC-D10-RA-BK/S9205-ND/1990098)) |
| J4        | 01x03 Female pinsocket                                                                                                                                  |
| J5        | 02x05 Male IDC header                                                                                                                                   |
| J6        | 01x03 Male pinheader (+ jumper)                                                                                                                         |
| J7        | 01x03 Male pinheader (+ jumper)                                                                                                                         |
| R1        | 1 kΩ 0805 Resistor                                                                                                                                      |
| R2        | 100 Ω 0805 Resistor                                                                                                                                     |
| C1        | 100 nF 0805 Capacitor                                                                                                                                   |
| SW1       | 2 pin SPST tact switch                                                                                                                                  |

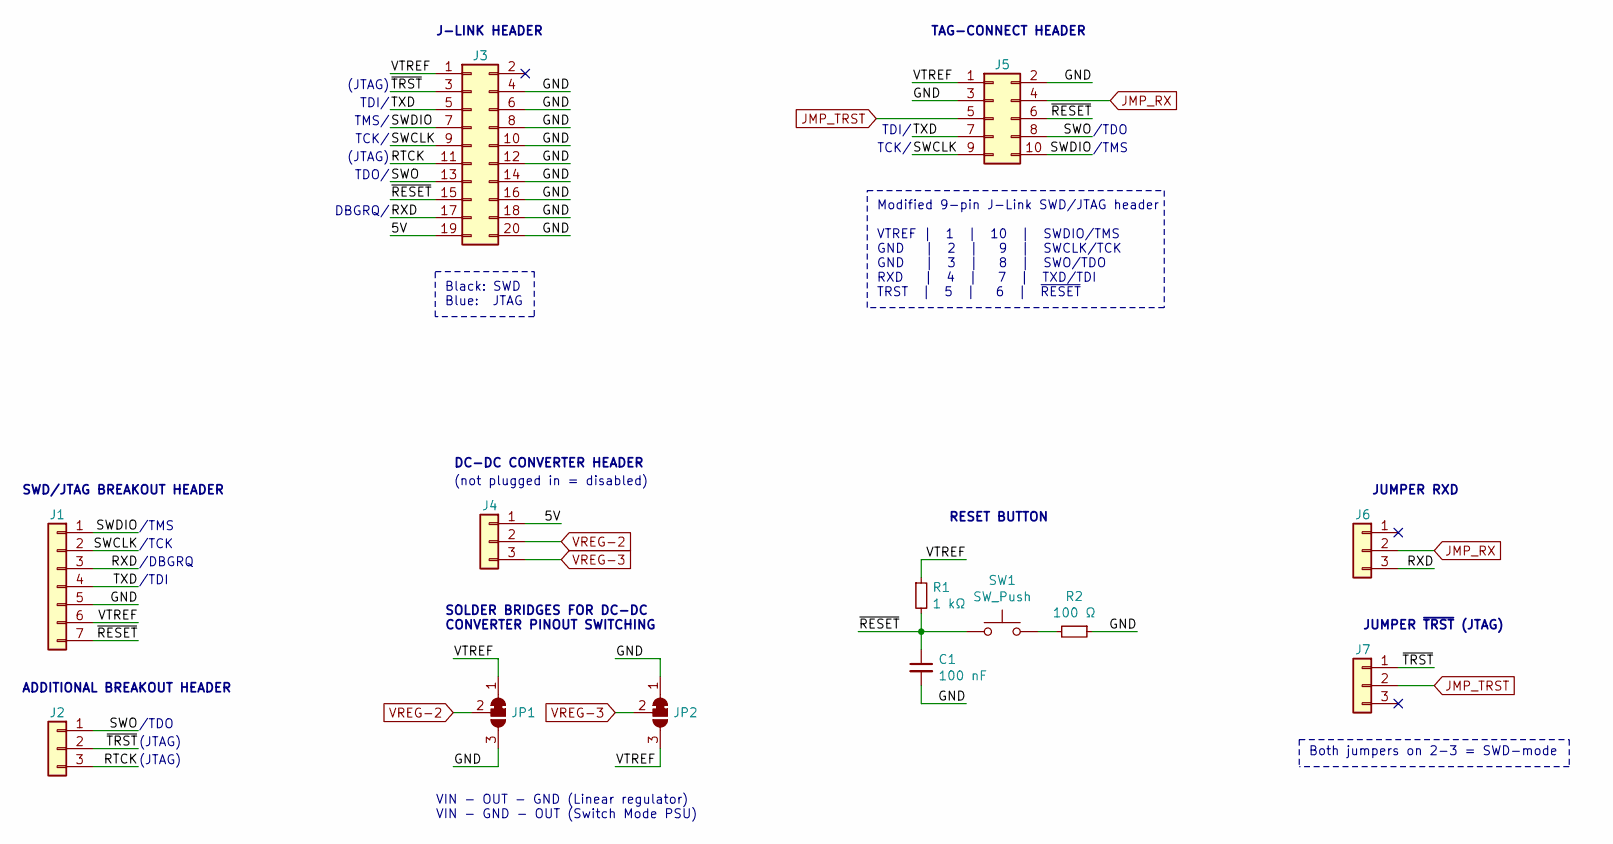
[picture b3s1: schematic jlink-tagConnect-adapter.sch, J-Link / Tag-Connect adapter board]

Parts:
C1: 100 nF; C_0805_2012Metric_Pad1.15x1.40mm_HandSolder
J1: Conn_01x07; PinHeader_1x07_P2.54mm_Vertical
J2, J6, J7: Conn_01x03; PinHeader_1x03_P2.54mm_Vertical
J3: Conn_02x10_Odd_Even; PinSocket_2x10_P2.54mm_Horizontal
J4: Conn_01x03; PinSocket_1x03_P2.54mm_Vertical
J5: Conn_02x05_Odd_Even; IDC-Header_2x05_P2.54mm_Vertical
JP1, JP2: SolderJumper_3_Bridged12; SolderJumper-3_P1.3mm_Bridged12_Pad1.0x1.5mm_NumberLabels
R1: 1 kΩ; R_0805_2012Metric_Pad1.15x1.40mm_HandSolder
R2: 100 Ω; R_0805_2012Metric_Pad1.15x1.40mm_HandSolder
SW1: SW_Push; SW_SPST_FSMSM

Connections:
/5V: J3.19, J4.1
/GND: C1.2, J1.5, J3.4, J3.6, J3.8, J3.10, J3.12, J3.14, J3.16, J3.18, J3.20, J5.2, J5.3, JP1.3 (B), JP2.1 (A), R2.1
/RTCK: J2.3, J3.11
/RXD: J1.3, J3.17, J6.3
/SWCLK: J1.2, J3.9, J5.9
/SWDIO: J1.1, J3.7, J5.10
/SWO: J2.1, J3.13, J5.8
/TXD: J1.4, J3.5, J5.7
/VTREF: J1.6, J3.1, J5.1, JP1.1 (A), JP2.3 (B), R1.1
/~RESET: C1.1, J1.7, J3.15, J5.6, R1.2, SW1.1
/~TRST: J2.2, J3.3, J7.1
JMP_RX: J5.4, J6.2
JMP_TRST: J5.5, J7.2
unnamed: R2.2, SW1.2
VREG-2: J4.2, JP1.2 (C)
VREG-3: J4.3, JP2.2 (C)

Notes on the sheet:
JUMPER RXD
/TDO
/TMS
TCK/
TDI/
TDO/
TMS/
DBGRQ/
Black: SWD Blue: JTAG
(JTAG)
JUMPER ~TRST~ (JTAG)
RESET BUTTON
SWD/JTAG BREAKOUT HEADER
VIN - OUT - GND (Linear regulator) VIN - GND - OUT (Switch Mode PSU)
ADDITIONAL BREAKOUT HEADER
/TCK
/DBGRQ
/TDI
Modified 9-pin J-Link SWD/JTAG header VTREF | 1 | 10 | SWDIO/TMS GND | 2 | 9 | SWCLK/TCK GND | 3 | 8 | SWO/TDO RXD | 4 | 7 | TXD/TDI TRST | 5 | 6 | ~RESET
TAG-CONNECT HEADER
SOLDER BRIDGES FOR DC-DC CONVERTER PINOUT SWITCHING
Both jumpers on 2-3 = SWD-mode
J-LINK HEADER
DC-DC CONVERTER HEADER
(not plugged in = disabled)

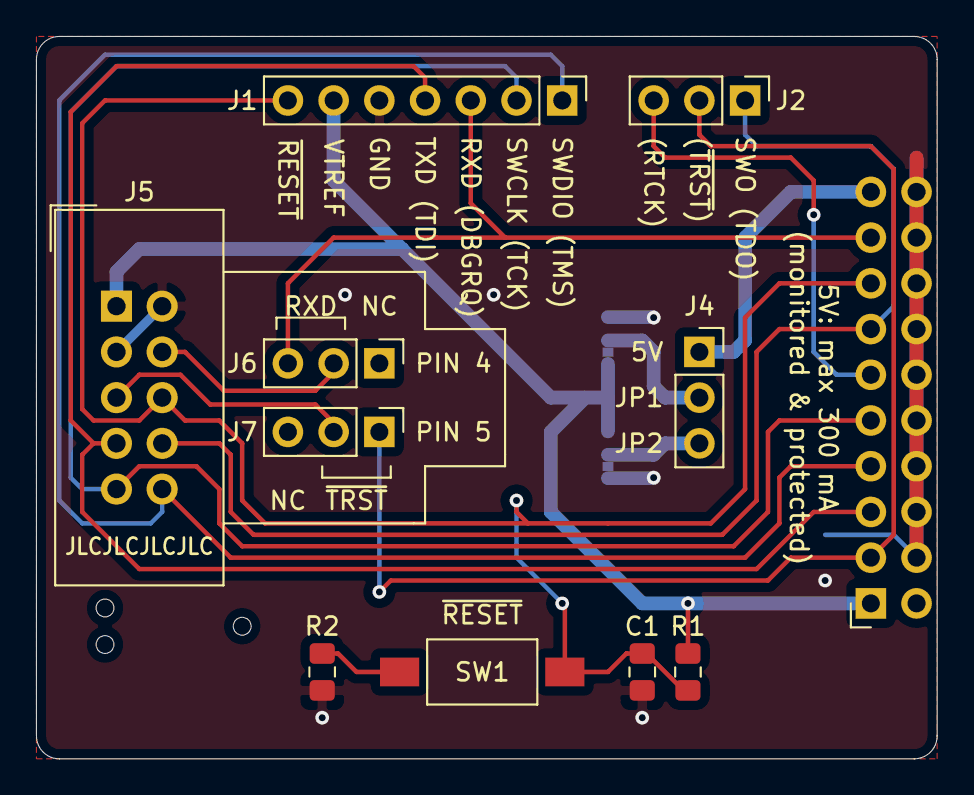
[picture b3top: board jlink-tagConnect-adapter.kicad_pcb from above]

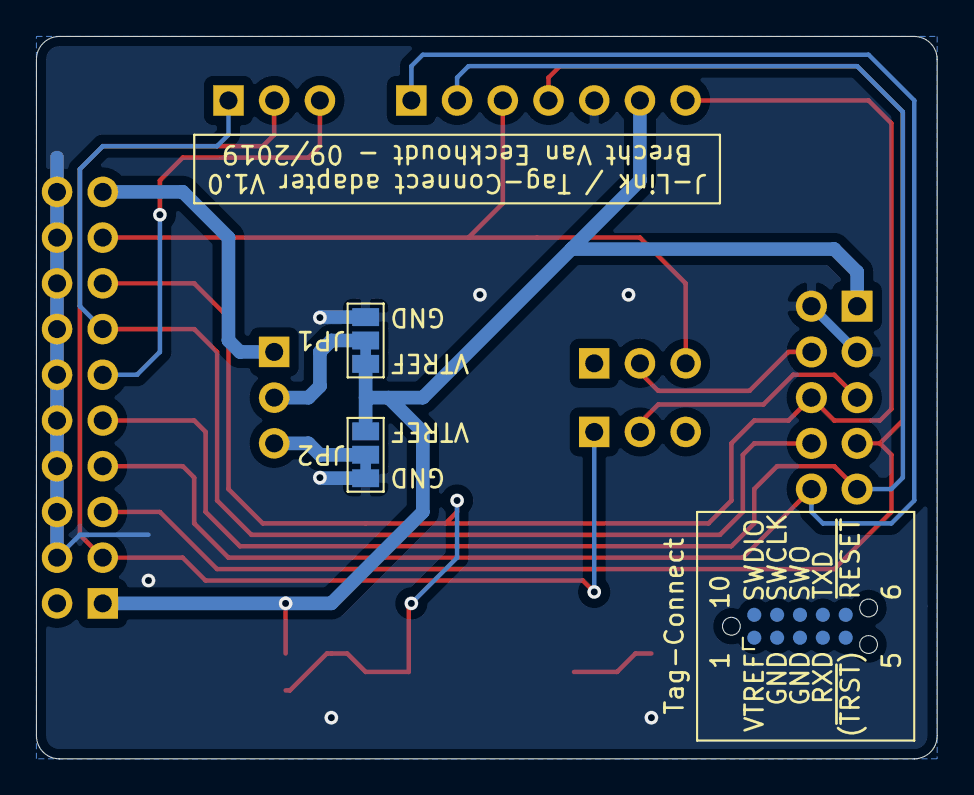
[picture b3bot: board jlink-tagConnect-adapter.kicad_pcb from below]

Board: 2 copper layers, 50.0 x 40.1 mm, 13 parts (2 on the bottom side), 16 nets.

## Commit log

2019-09-19 Upload initial release
2019-09-19 Add documentation
2019-09-19 Move datasheet
2019-09-19 Rename datasheet
2019-09-19 Added note to schematic about RTCK connection
2019-11-25 Updated licence
2019-11-25 Moved first hardware files to v1 folder
2019-11-25 Added datasheets
2019-11-25 Moved first hardware pictures to v1 folder
2019-11-25 Added pinouts
2019-11-25 Added v2 schematic
2019-11-26 Changed OSHW logo
2019-11-26 Updated with new debug header symbols
2019-11-28 Started moving old hardware documentation
2019-11-28 Finalized PCB layout
2019-11-28 Added 3D models
2019-11-28 Updated schematic with new title
2019-11-28 Updated 3D models
2019-11-28 Updated PCB with new 3D models
2019-11-28 Added pictures
2019-11-28 Moved hardware revision v1.0 documentation
2019-11-28 Updated documentation
2019-11-28 Fixed typo
2019-11-28 Updated BOM
2019-12-03 Updated readme with new BOM
2019-12-10 Added gerber files
2020-01-07 Added future improvements
2020-01-14 Update README.md
    Fixed 9 pin FTSH type
2020-01-14 Update cache
2020-02-19 Added additional pictures
2020-12-10 Added V3.0 hardware files
2020-12-10 Added V3.0 PCB pictures
2020-12-10 Added V3.0 hardware changes
2020-12-10 Updated README file to reflect hardware V3.0
2020-12-10 Moved V2.0 README
2020-12-10 Updated image paths
2020-12-11 Added extra link to gerber files
2020-12-11 Fixed link
2020-12-11 Added author and date
2020-12-26 Added JLCPCB order number position
2021-08-30 Added info about J-Link RTT
2021-08-30 Update spacing
2025-03-20 Changed/added J-Link Commander commands ## Updated wiki links
2025-03-20 Added more space in the command table
2025-03-20 Version 4 upload
2025-03-20 Uploaded v4 gerbers
2025-03-20 Generated v4 gerbers
2025-03-21 Added serial flashing info ## Updated BOM ## Changed section order
2025-03-21 Added commands ## Added serial flashing info
2025-03-21 Removed TODO
2025-03-27 Added v4 picture
2025-03-27 Updated partnumber in BOM
2025-03-29 Small documentation updates
2025-03-30 Added more command (info) ## Added more links
2025-03-31 Small documentation changes/additions
2025-03-31 Switching back to png ## Tiny documentation changes

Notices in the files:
README.md:
License: CERN OHL v.1.2
hardware/jlink-tagConnect-adapter-v2/jlink-tagConnect-adapter-v2.kicad_pcb:
Licensed under CERN OHL v.1.2
